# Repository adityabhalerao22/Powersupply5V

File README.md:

# Powersupply5V
Kicad Schematic, PCB and gerber files for low noise 5V dual power supply.

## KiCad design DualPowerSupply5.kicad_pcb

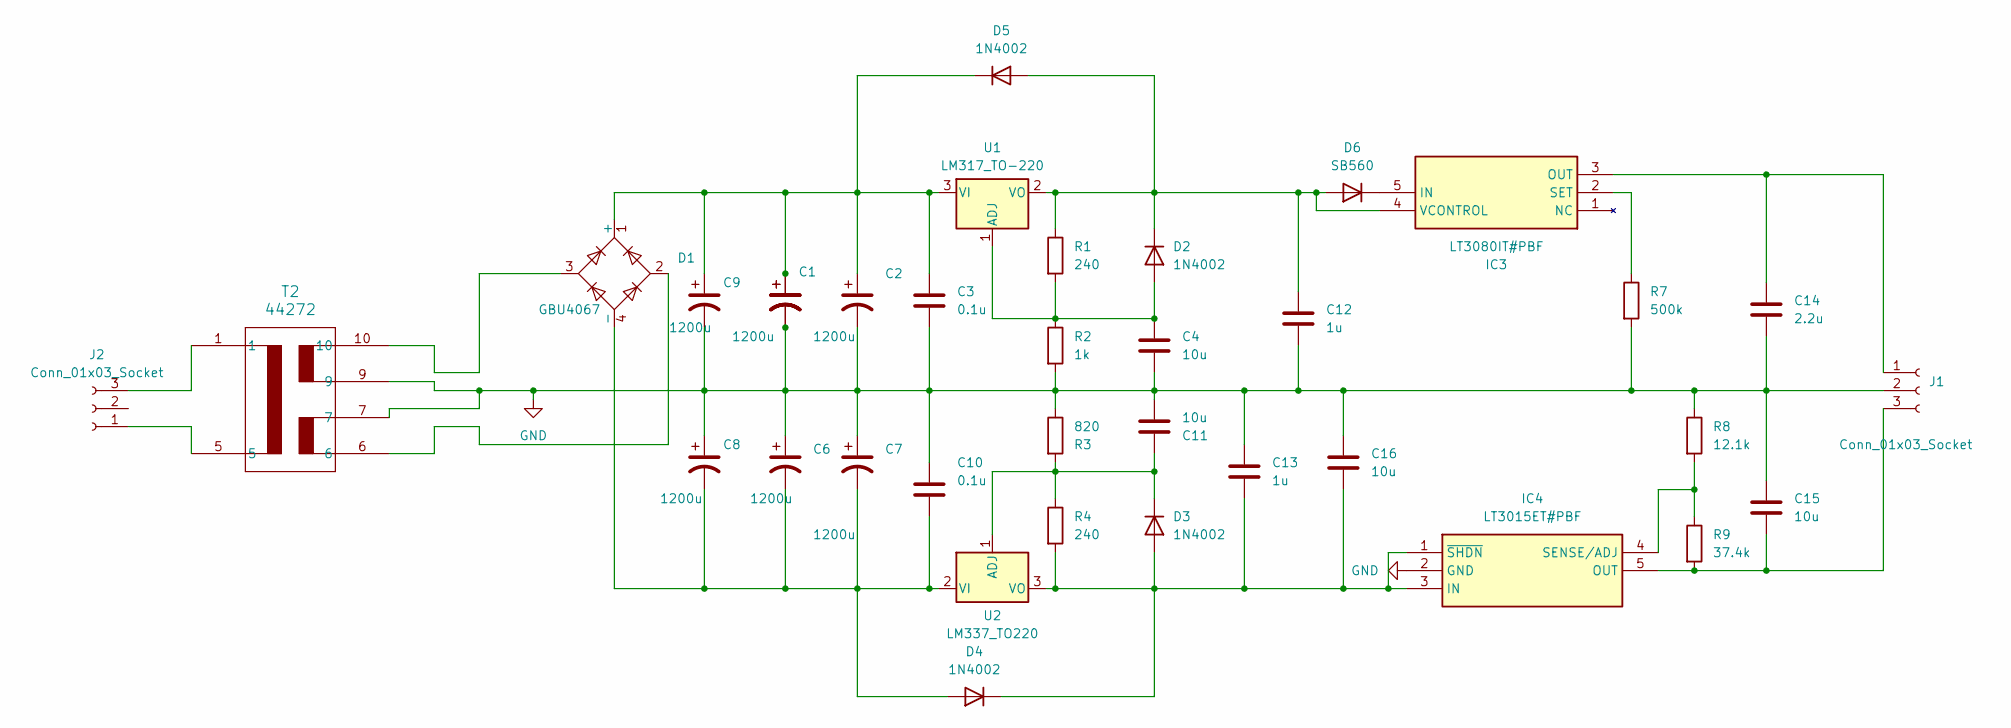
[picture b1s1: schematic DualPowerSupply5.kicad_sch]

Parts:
C1, C2, C5, C6, C7, C8, C9: 1200u; CP_Radial_D10.0mm_P5.00mm
C3, C10: 0.1u; C_Rect_L9.0mm_W3.2mm_P7.50mm_MKT
C4, C11, C15, C16: 10u; C_Rect_L9.0mm_W3.2mm_P7.50mm_MKT
C12, C13: 1u; C_Rect_L9.0mm_W3.2mm_P7.50mm_MKT
C14: 2.2u; C_Rect_L9.0mm_W3.2mm_P7.50mm_MKT
D1: GBU4067; Diode_Bridge_Vishay_GBU
D2, D3, D4, D5: 1N4002; D_DO-41_SOD81_P10.16mm_Horizontal
D6: SB560; D_DO-201AD_P12.70mm_Horizontal
IC3: LT3080IT#PBF; TO170P457X1022X2306-5P; Manufacturer_Part_Number LT3080IT#PBF
IC4: LT3015ET#PBF; TO170P457X1022X2306-5P; Manufacturer_Part_Number LT3015ET#PBF
J1, J2: Conn_01x03_Socket; CTB01003
R1, R4: 240; R_Axial_DIN0207_L6.3mm_D2.5mm_P7.62mm_Horizontal
R2: 1k; R_Axial_DIN0207_L6.3mm_D2.5mm_P7.62mm_Horizontal
R3: 820; R_Axial_DIN0207_L6.3mm_D2.5mm_P7.62mm_Horizontal
R7: 500k; R_Axial_DIN0207_L6.3mm_D2.5mm_P7.62mm_Horizontal
R8: 12.1k; R_Axial_DIN0207_L6.3mm_D2.5mm_P7.62mm_Horizontal
R9: 37.4k; R_Axial_DIN0207_L6.3mm_D2.5mm_P7.62mm_Horizontal
T2: 44272
U1: LM317_TO-220; TO-220-3_Vertical
U2: LM337_TO220; TO-220-3_Vertical

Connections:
GND: C1.2, C2.2, C3.2, C4.2, C5.2, C6.1, C7.1, C8.1, C9.2, C10.1, C11.1, C12.2, C13.1, C14.2, C15.1, C16.1, IC4.2 (GND), J1.2, R2.2, R3.1, R7.2, R8.1, T2.7, T2.9
unnamed: C1.1, C2.1, C3.1, C5.1, C9.1, D1.1 (+), D5.1 (K), U1.3 (VI)
unnamed: C6.2, C7.2, C8.2, C10.2, D1.4 (-), D4.2 (A), U2.2 (VI)
unnamed: D1.2, T2.6
unnamed: D1.3, T2.10
unnamed: C4.1, D2.2 (A), R1.2, R2.1, U1.1 (ADJ)
unnamed: C12.1, D2.1 (K), D5.2 (A), D6.2 (A), IC3.4 (VCONTROL), R1.1, U1.2 (VO)
unnamed: C13.2, C16.2, D3.2 (A), D4.1 (K), IC4.1 (~SHDN), IC4.3 (IN), R4.2, U2.3 (VO)
unnamed: C11.2, D3.1 (K), R3.2, R4.1, U2.1 (ADJ)
unnamed: D6.1 (K), IC3.5 (IN)
unnamed: C14.1, IC3.3 (OUT), J1.1
unnamed: IC3.2 (SET), R7.1
unnamed: C15.2, IC4.5 (OUT), J1.3, R9.2
unnamed: IC4.4 (SENSE/ADJ), R8.2, R9.1
unnamed: J2.1, T2.5
unnamed: J2.3, T2.1

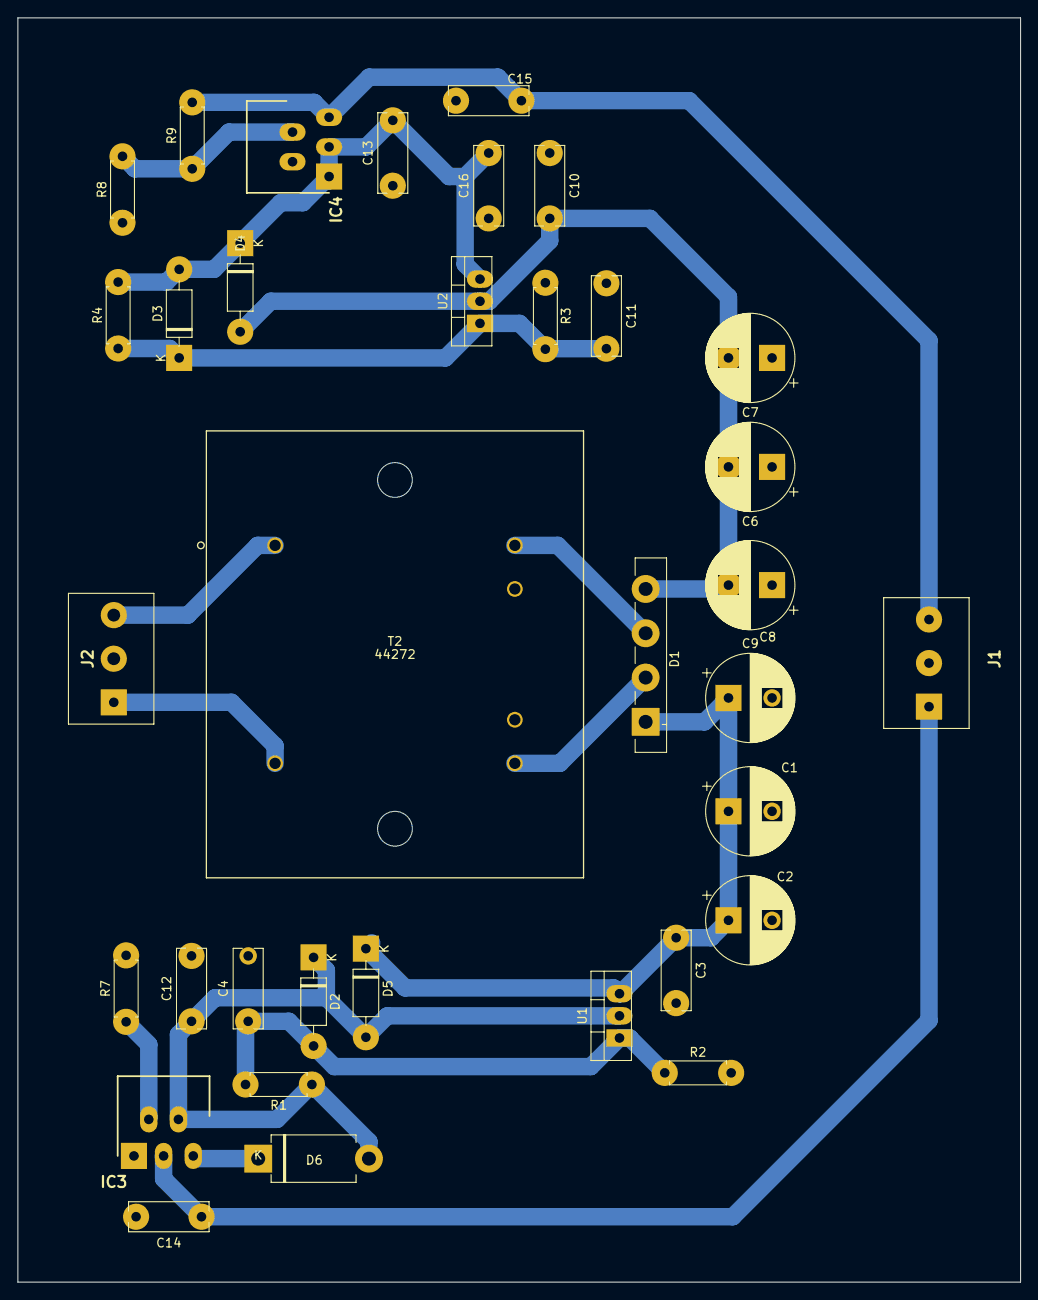
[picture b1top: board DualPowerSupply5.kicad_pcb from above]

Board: 2 copper layers, 115.0 x 145.0 mm, 35 parts (0 on the bottom side), 16 nets.

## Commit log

2025-07-05 Add files via upload
    First commit

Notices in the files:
parts and their libraries:
Copyright 2016 Accelerated Designs. All rights reserved.
